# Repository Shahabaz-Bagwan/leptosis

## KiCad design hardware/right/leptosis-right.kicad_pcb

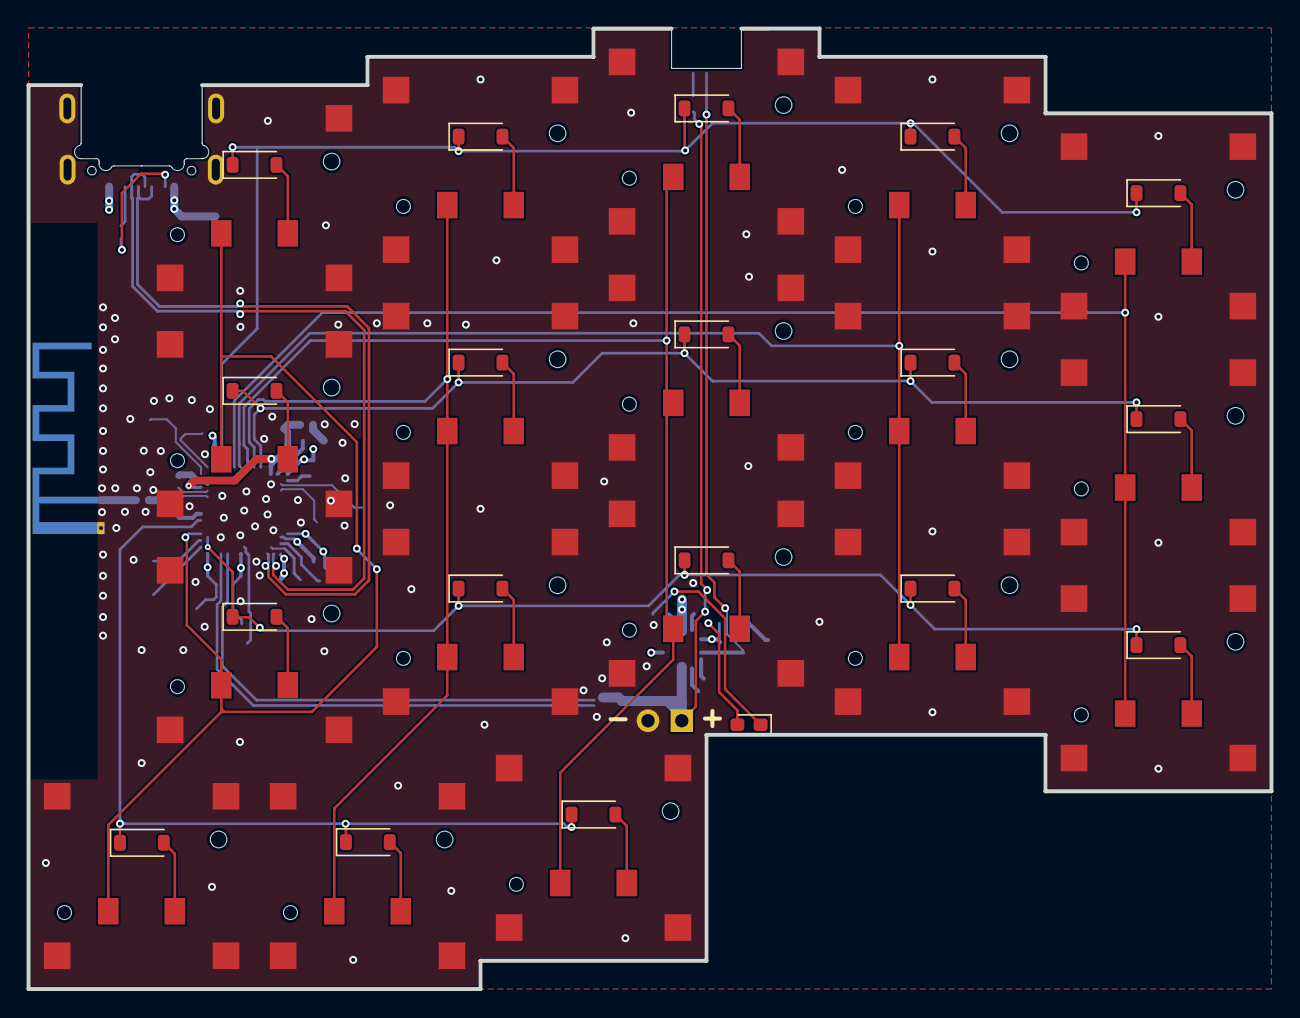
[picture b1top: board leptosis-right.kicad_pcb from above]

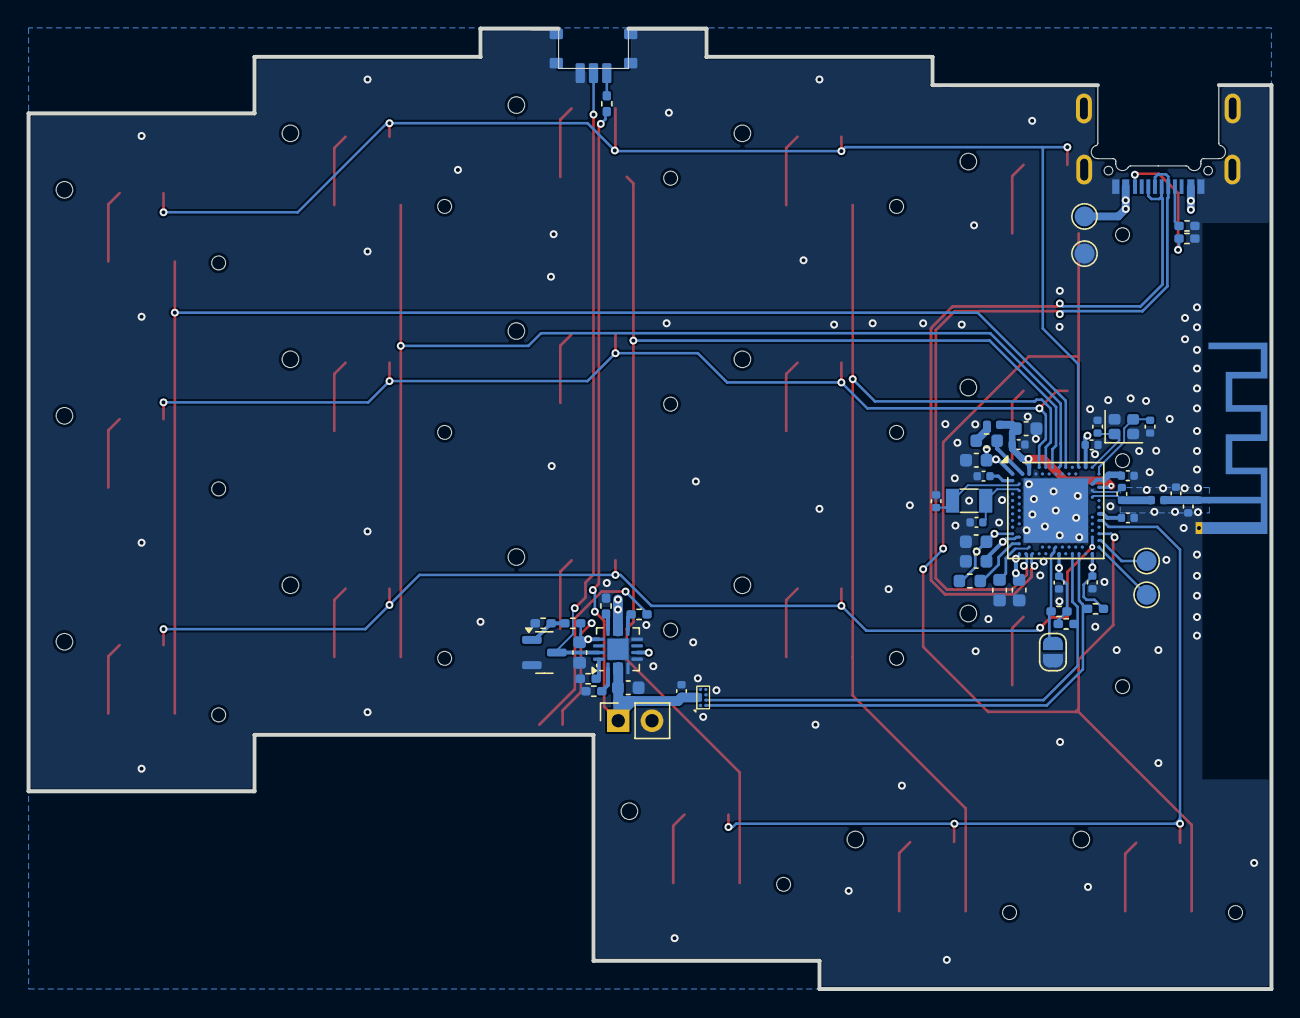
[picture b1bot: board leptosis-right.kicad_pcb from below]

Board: 4 copper layers, 93.5 x 72.3 mm, 91 parts (54 on the bottom side), 63 nets.

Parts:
AE1: Antenna_Shield; Texas_SWRA117D_2.4GHz_Left
C1, C2, C3, C4: 15pF; C_0402_1005Metric
C5: 0.8pF; C_0402_1005Metric
C6: 0.5pF; C_0402_1005Metric
C7: NC; C_0402_1005Metric
C8, C18, C19, C20, C23: 100nF; C_0402_1005Metric
C9: 100pF; C_0402_1005Metric
C10: 820pF; C_0402_1005Metric
C11, C17: 1uF; C_0603_1608Metric
C12: 47nF; C_0402_1005Metric
C13, C14, C15, C16, C21, C22: 4.7uF; C_0603_1608Metric
D1, D2, D3, D4, D5, D7, D8, D9, D10, D11, D13, D14, D15, D16, D17, D21, D22, D23: 1N4148W; D_SOD-123
D31: LED; LED_0603_1608Metric_Pad1.05x0.95mm_HandSolder
J1: USB_C_Receptacle_USB2.0_14P; USB_C_Receptacle_HRO_TYPE-C-31-M-14
J2: Conn_01x02; PinSocket_1x02_P2.54mm_Vertical
JP1: SolderJumper_2_Open; SolderJumper-2_P1.3mm_Open_RoundedPad1.0x1.5mm
L1: 4.7nH; L_0402_1005Metric
L2, L4: 10uH; L_0603_1608Metric
L3: 15nH; L_0402_1005Metric
Q2: 2N7002; SOT-23
R1, R2, R15, R16: 5.1k; R_0402_1005Metric_Pad0.72x0.64mm_HandSolder
R3, R6, R8, R10: 10k; R_0402_1005Metric_Pad0.72x0.64mm_HandSolder
R4: 3.9k; R_0402_1005Metric_Pad0.72x0.64mm_HandSolder
R5, R9: 1.5k; R_0402_1005Metric_Pad0.72x0.64mm_HandSolder
R7: 100; R_0402_1005Metric_Pad0.72x0.64mm_HandSolder
SW2, SW3, SW4, SW5, SW6, SW8, SW9, SW10, SW11, SW12, SW14, SW15, SW16, SW17, SW18, SW22, SW23, SW24: SW_Push; SW_PG1316S
SW31: SW_SPDT; Switch_Sink_MINI_MSK12CO2
TP1, TP2, TP3, TP4: TestPoint; TestPoint_Pad_D1.5mm
U1: nRF52840; Nordic_AQFN-73-1EP_7x7mm_P0.5mm
U2: BQ24075RGT; VQFN-16-1EP_3x3mm_P0.5mm_EP1.6x1.6mm
U3: MAX17048X; WLP-8_1.67x0.93_P0.4
Y1: 32MHz 12pF; Crystal_SMD_2016-4Pin_2.0x1.6mm
Y2: 32.768kHz 12.5pF; Crystal_SMD_3215-2Pin_3.2x1.5mm

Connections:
+5V: C15.1, D31.2 (A), U1.Y2 (VDDH), U2.6 (EN1), U2.10 (OUT), U2.11 (OUT)
+BATT: C21.1, C23.1, J2.1, R8.2, U2.2 (BAT), U2.3 (BAT), U3.A2 (CELL), U3.A3 (VDD)
/COL0: SW2.1, SW8.1, SW14.1, U1.A16 (P1.13)
/COL1: SW3.1, SW9.1, SW15.1, U1.A14 (P1.15)
/COL2: SW4.1, SW10.1, SW16.1, SW22.1, U1.A12 (AIN0/P0.02)
/COL3: SW5.1, SW11.1, SW17.1, SW23.1, U1.A10 (AIN5/P0.29)
/COL4: SW6.1, SW12.1, SW18.1, SW24.1, U1.W24 (P1.02)
/D+: J1.A6 (D+), J1.B6 (D+), U1.AD6 (D+)
/D-: J1.A7 (D-), J1.B7 (D-), U1.AD4 (D-)
/DEC1: C8.2, U1.C1 (DEC1)
/DEC3: C9.2, U1.D23 (DEC3)
/DEC4_6: C11.2, C12.2, L3.2, U1.B5 (DEC4), U1.E24 (DEC6)
/DEC5: C10.2, U1.N24 (DEC5)
/DECUSB: C13.2, U1.AC5 (DECUSB)
/ROW0: D1.1 (K), D2.1 (K), D3.1 (K), D4.1 (K), D5.1 (K), U1.A20 (P1.10)
/ROW1: D7.1 (K), D8.1 (K), D9.1 (K), D10.1 (K), D11.1 (K), U1.A8 (AIN7/P0.31)
/ROW2: D13.1 (K), D14.1 (K), D15.1 (K), D16.1 (K), D17.1 (K), U1.Y23 (P1.01)
/ROW3: D21.1 (K), D22.1 (K), D23.1 (K), U1.R24 (P1.06)
/SCL: R15.1, U1.AD18 (P0.22), U3.B2 (SCL)
/SDA: R16.1, U1.AD20 (P0.24), U3.B1 (SDA)
/SYSOFF: Q2.3 (D), SW31.2 (B), U2.15 (SYSOFF)
/~RESET: JP1.2 (B), R3.2, U1.AC13 (P0.18/~RESET), U1.AD12 (P0.17)
GND: AE1.2 (Shield), C1.1, C2.1, C3.2, C4.2, C5.2, C6.2, C7.2, C8.1, C9.1, C10.1, C11.1, C12.1, C13.1, C14.2, C15.2, C16.2, C17.2, C18.2, C19.2, C20.2, C21.2, C22.2, C23.2, J1.A1 (GND), J1.A12 (GND), J1.B1 (GND), J1.B12 (GND), J1.S1 (SHIELD), J2.2, JP1.1 (A), Q2.2 (S), R1.2, R2.2, R4.1, R5.1, R6.1, R10.1, SW2.MP, SW3.MP, SW4.MP, SW5.MP, SW6.MP, SW8.MP, SW9.MP, SW10.MP, SW11.MP, SW12.MP, SW14.MP, SW15.MP, SW16.MP, SW17.MP, SW18.MP, SW22.MP, SW23.MP, SW24.MP, SW31.3 (C), SW31.MT, TP4.1, U1.B7 (VSS), U1.EP (VSS), U1.F23 (VSS_PA), U2.4 (~CE), U2.5 (EN2), U2.8 (VSS), U2.17 (VSS), U3.A1 (CTG), U3.A4 (GND), U3.B3 (QSTRT), Y1.2, Y1.4
unnamed: AE1.1 (A), C6.1, C7.1, L1.1
unnamed: D1.2 (A), SW2.2
unnamed: D2.2 (A), SW3.2
unnamed: D3.2 (A), SW4.2
unnamed: D4.2 (A), SW5.2
unnamed: D5.2 (A), SW6.2
unnamed: D7.2 (A), SW8.2
unnamed: D8.2 (A), SW9.2
unnamed: D9.2 (A), SW10.2
unnamed: D10.2 (A), SW11.2
unnamed: D11.2 (A), SW12.2
unnamed: D13.2 (A), SW14.2
unnamed: D14.2 (A), SW15.2
unnamed: D15.2 (A), SW16.2
unnamed: D16.2 (A), SW17.2
unnamed: D17.2 (A), SW18.2
unnamed: D21.2 (A), SW22.2
unnamed: D22.2 (A), SW23.2
unnamed: D23.2 (A), SW24.2
unnamed: D31.1 (K), R9.2
unnamed: J1.A5 (CC1), R1.1
unnamed: J1.B5 (CC2), R2.1
unnamed: L2.2, L3.1
unnamed: Q2.1 (G), R6.2, R7.1
unnamed: R8.1, SW31.1 (A)
unnamed: C5.1, L1.2, U1.H23 (ANT)
unnamed: L2.1, U1.B3 (DCC)
unnamed: L4.1, U1.AB2 (DCCH)
unnamed: TP1.1, U1.AA24 (SWDCLK)
unnamed: TP2.1, U1.AC24 (SWDIO)
unnamed: C1.2, U1.B24 (XC1), Y1.3
unnamed: C2.2, U1.A23 (XC2), Y1.1
unnamed: C3.1, U1.D2 (XL1/P0.00), Y2.2
unnamed: C4.1, U1.F2 (XL2/P0.01), Y2.1
unnamed: R5.2, U2.12 (ILIM)
unnamed: R4.2, U2.16 (ISET)
unnamed: R10.2, U2.1 (TS)
unnamed: R9.1, U2.9 (~CHG)
VBUS: C14.1, C22.1, J1.A4 (VBUS), J1.A9 (VBUS), J1.B4 (VBUS), J1.B9 (VBUS), R7.2, TP3.1, U1.AD2 (VBUS), U2.13 (IN)
VDD_nRF: C16.1, C17.1, C18.1, C19.1, C20.1, L4.2, R3.1, R15.2, R16.2, U1.A22 (VDD), U1.AD14 (VDD), U1.AD23 (VDD), U1.B1 (VDD), U1.W1 (VDD)

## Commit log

2025-09-08 chore(chocofi): create chocofi layout with ULP
